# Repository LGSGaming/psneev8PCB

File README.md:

# PSnee V8 PCB

Compact PCB designed for PSnee v8 code by postal2201. Firmware can be found [here](https://github.com/postal2201/PSNee_V8). Treat project as in beta as PCB has not been tested yet. Manufacture at your own risk.

## Contributing

Pull requests are welcome

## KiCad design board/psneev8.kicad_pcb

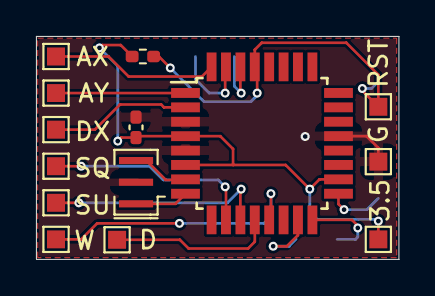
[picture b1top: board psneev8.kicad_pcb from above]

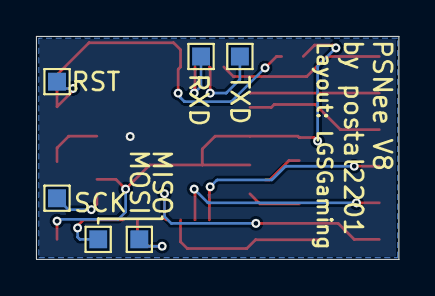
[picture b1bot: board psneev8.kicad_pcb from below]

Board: 2 copper layers, 20.1 x 12.4 mm, 19 parts (5 on the bottom side), 17 nets.

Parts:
C1: 100nf; C_0402_1005Metric_Pad0.74x0.62mm_HandSolder
R1: 10k; R_0402_1005Metric_Pad0.72x0.64mm_HandSolder
TP1: 3.5; TestPoint_Pad_1.0x1.0mm
TP2: G; TestPoint_Pad_1.0x1.0mm
TP3: DX; TestPoint_Pad_1.0x1.0mm
TP4: AX; TestPoint_Pad_1.0x1.0mm
TP5: SQ; TestPoint_Pad_1.0x1.0mm
TP6: SU; TestPoint_Pad_1.0x1.0mm
TP7: D; TestPoint_Pad_1.0x1.0mm
TP8: W; TestPoint_Pad_1.0x1.0mm
TP9: AY; TestPoint_Pad_1.0x1.0mm
TP10: RST; TestPoint_Pad_1.0x1.0mm
TP11: RXD; TestPoint_Pad_1.0x1.0mm
TP12: TXD; TestPoint_Pad_1.0x1.0mm
TP13: SCK; TestPoint_Pad_1.0x1.0mm
TP14: MOSI; TestPoint_Pad_1.0x1.0mm
TP15: MISO; TestPoint_Pad_1.0x1.0mm
U1: ATmega328P-A; TQFP-32_7x7mm_P0.8mm
Y1: 16mhz; Resonator_SMD_Murata_CSTxExxV-3Pin_3.0x1.1mm

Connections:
AX: TP4.1, U1.32 (PD2)
AY: TP9.1, U1.1 (PD3)
DATA: TP7.1, U1.12 (PB0)
DX: TP3.1, U1.2 (PD4)
GND: C1.2, TP2.1, U1.3 (GND), U1.5 (GND), U1.21 (GND), Y1.2
MISO: TP15.1, U1.16 (PB4)
MOSI: TP14.1, U1.15 (PB3)
unnamed: U1.7 (XTAL1/PB6), Y1.3
unnamed: U1.8 (XTAL2/PB7), Y1.1
RESET: R1.2, TP10.1, U1.29 (~RESET/PC6)
RXD: TP11.1, U1.30 (PD0)
SCK: TP13.1, U1.17 (PB5)
SQCK: TP5.1, U1.10 (PD6)
SUBQ: TP6.1, U1.11 (PD7)
TXD: TP12.1, U1.31 (PD1)
VCC: C1.1, R1.1, TP1.1, U1.4 (VCC), U1.6 (VCC), U1.18 (AVCC)
WFCK: TP8.1, U1.13 (PB1)

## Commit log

2024-03-07 Files added
    None
2024-03-13 added schematic
